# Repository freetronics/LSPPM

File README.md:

Freetronics LibreSat Payload Processor Module
=============================================
Copyright 2013-2017 Freetronics Pty Ltd  
Freetronics site:  www.freetronics.com  
Freetronics email: info@freetronics.com  

A CubeSat payload board that incorporates 16 processor nodes for
running experiments, and a supervisor processor node to control
the experiment nodes.

A previous version of this board flew in space on ArduSat-X and
ArduSat-1.

Features:

 * 16 x processor nodes, each with an ATmega328P MCU
 * Each processor node runs the Arduino bootloader
 * 1 x supervisor node with an ATmega2561
 * Micro SD card slot connected to supervisor
 * All MCUs and sensors on a shared I2C bus
 * All I2C devices use bidirectional isolation circuits to allow continued operation of the system with failed devices
 * Processor node UARTs connected via multiplexers to the supervisor's first UART
 * 5V serial debug console with standard FTDI-style pinout on supervisor's second UART
 * Each processor node can be powered down independently by the supervisor
 * Each processor node can be reset using an I2C latch by the supervisor
 * Each MCU has an independent crystal for maximum reliability
 * TX, RX, and D13 LEDs on every processor node
 * Top and bottom temperature sensors on I2C bus with "disable" option to prevent address collisions
 * Requires external 5V and 3.3V supply
 * Current consumption monitoring of both power rails by the supervisor
 * Stackable CubeSat bus connectors
 * Conforms to CubeSat mechanical standards for dimensions and mounting
 * Selectable power bus connections
 * Optional I2C satellite bus pull-ups
 * I2C headers for spectrometer, Geiger counter, and bottom plate sensor assembly
 * GPS header with UART connections to node 11 via 3.3V level shifters
 * Switchable power supply to GPS header controlled by supervisor
 * Stackable CubeSat Bus connectors

Specifications:

 * Dimensions: 95.45mm x 90.3mm
 * PCB material: FR4 fibreglass (requires out-gassing before vacuum use)
 * PCB finish: ENIG (electroless nickel immersion gold) recommended
 * Module mass: 37 grams
 * Connector mass (pair): 15 grams
 * Total assembled mass including solder: 54 grams

More information is available at:

  http://www.freetronics.com.au/lsppm

INSTALLATION
------------
The design is saved as an EAGLE project. EAGLE PCB design software is
available from www.cadsoftusa.com free for non-commercial use. To use
this project download it and place the directory containing these files
into the "eagle" directory on your computer. Then open EAGLE and
navigate to the project. 

DISTRIBUTION
------------
The specific terms of distribution of this project are governed by the
license referenced below.

LICENSE
-------
Licensed under the TAPR Open Hardware License (www.tapr.org/OHL).
The "license" folder within this repository also contains a copy of
this license in plain text format.

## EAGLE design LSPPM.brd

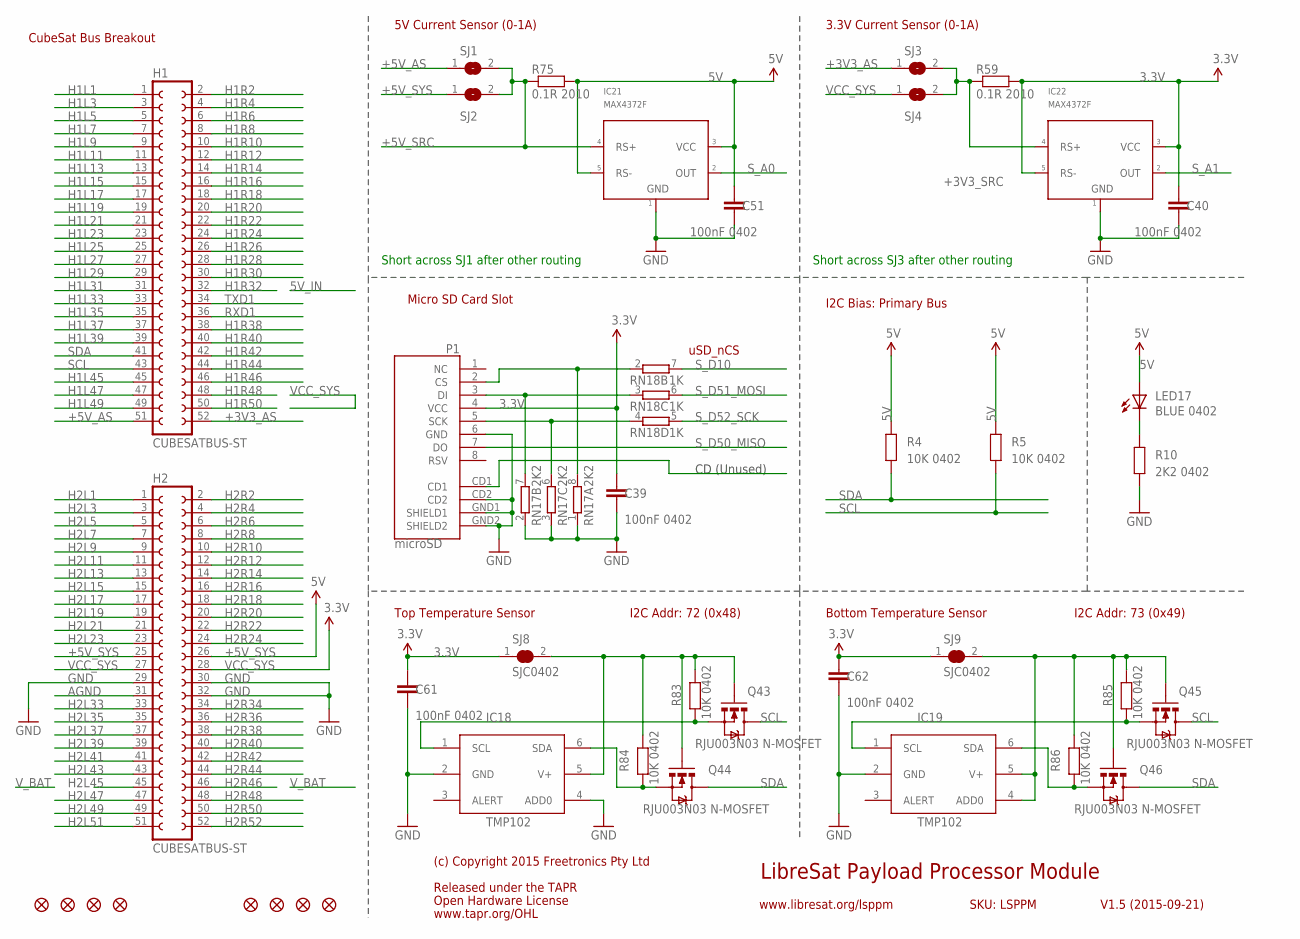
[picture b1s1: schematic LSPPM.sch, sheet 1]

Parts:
C39, C40, C51, C61, C62: 100nF 0402; C0402
FID1, FID2, FID3, FID4, FID5, FID6, FID7, FID8: FIDUCIAL1X2.5; FIDUCIAL-1X2.5
H1, H2: CUBESATBUS-ST
IC18, IC19: TMP102; SOT563
IC21, IC22: MAX4372F; SOT23-5
LED17: BLUE 0402; LED-0402
P1: microSD; MICRO-SD-SOCKET-PP
Q43, Q44, Q45, Q46: RJU003N03 N-MOSFET; SOT32-3
R4, R5, R83, R84, R85, R86: 10K 0402; R0402
R10: 2K2 0402; R0402
R59, R75: 0.1R 2010; R2010
RN17: 2K2; CAY16
RN18: 1K; CAY16
SJ1, SJ2, SJ3, SJ4: SJ
SJ8, SJ9: SJC0402; 0402SJC

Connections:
3.3V: C39.1, C40.1, C61.1, C62.1, IC22.3 (VCC), IC22.5 (RS-), P1.4 (VCC), R59.2, SJ8.1, SJ9.1; also elsewhere on the board
5V: C51.1, IC21.3 (VCC), IC21.5 (RS-), LED17.A, R4.2, R5.2, R75.2; also elsewhere on the board
+3V3_AS: H1.52, SJ3.1
+3V3_SRC: IC22.4 (RS+), R59.1, SJ3.2, SJ4.2
+5V_AS: H1.51, SJ1.1
+5V_SRC: IC21.4 (RS+), R75.1, SJ1.2, SJ2.2; also elsewhere on the board
+5V_SYS: H2.25, H2.26, SJ2.1
AGND: H2.31
GND: C39.2, C40.2, C51.2, C61.2, C62.2, H2.29, H2.30, H2.32, IC18.2 (GND), IC18.4 (ADD0), IC19.2 (GND), IC21.1 (GND), IC22.1 (GND), P1.6 (GND), P1.CD2, P1.GND1 (SHIELD1), P1.GND2 (SHIELD2), R10.1, RN17.1, RN17.2 (1), RN17.3 (1); also elsewhere on the board
H1L1: H1.1
H1L3: H1.3
H1L5: H1.5
H1L7: H1.7
H1L9: H1.9
H1L11: H1.11
H1L13: H1.13
H1L15: H1.15
H1L17: H1.17
H1L19: H1.19
H1L21: H1.21
H1L23: H1.23
H1L25: H1.25
H1L27: H1.27
H1L29: H1.29
H1L31: H1.31
H1L33: H1.33
H1L35: H1.35
H1L37: H1.37
H1L39: H1.39
H1L45: H1.45
H1L47: H1.47
H1L49: H1.49
H1R2: H1.2
H1R4: H1.4
H1R6: H1.6
H1R8: H1.8
H1R10: H1.10
H1R12: H1.12
H1R14: H1.14
H1R16: H1.16
H1R18: H1.18
H1R20: H1.20
H1R22: H1.22
H1R24: H1.24
H1R26: H1.26
H1R28: H1.28
H1R30: H1.30
H1R32: H1.32
H1R38: H1.38
H1R40: H1.40
H1R42: H1.42
H1R44: H1.44
H1R46: H1.46
H1R48: H1.48
H1R50: H1.50
H2L1: H2.1
H2L3: H2.3
H2L5: H2.5
H2L7: H2.7
H2L9: H2.9
H2L11: H2.11
H2L13: H2.13
H2L15: H2.15
H2L17: H2.17
H2L19: H2.19
H2L21: H2.21
H2L23: H2.23
H2L33: H2.33
H2L35: H2.35
H2L37: H2.37
H2L39: H2.39
H2L41: H2.41
H2L43: H2.43
H2L45: H2.45
H2L47: H2.47
H2L49: H2.49
H2L51: H2.51
H2R2: H2.2
H2R4: H2.4
H2R6: H2.6
H2R8: H2.8
H2R10: H2.10
H2R12: H2.12
H2R14: H2.14
H2R16: H2.16
H2R18: H2.18
H2R20: H2.20
H2R22: H2.22
H2R24: H2.24
H2R34: H2.34
H2R36: H2.36
H2R38: H2.38
H2R40: H2.40
H2R42: H2.42
H2R44: H2.44
H2R46: H2.46
H2R48: H2.48
H2R50: H2.50
H2R52: H2.52
unnamed: LED17.C, R10.2
unnamed: P1.2 (CS), RN17.8 (2), RN18.2 (1)
unnamed: P1.3 (DI), RN17.7 (2), RN18.3 (1)
unnamed: P1.5 (SCK), RN17.6 (2), RN18.4 (1)
unnamed: IC18.1 (SCL), Q43.2 (S), R83.1
unnamed: IC18.6 (SDA), Q44.2 (S), R84.1
unnamed: IC19.6 (SDA), Q46.2 (S), R86.1
unnamed: IC19.1 (SCL), Q45.2 (S), R85.1
unnamed: IC18.5 (V+), Q43.1 (G), Q44.1 (G), R83.2, R84.2, SJ8.2
unnamed: IC19.4 (ADD0), IC19.5 (V+), Q45.1 (G), Q46.1 (G), R85.2, R86.2, SJ9.2
RXD1: H1.36; also elsewhere on the board
SCL: H1.43, Q43.3 (D), Q45.3 (D), R5.1; also elsewhere on the board
SDA: H1.41, Q44.3 (D), Q46.3 (D), R4.1; also elsewhere on the board
S_A0: IC21.2 (OUT); also elsewhere on the board
S_A1: IC22.2 (OUT); also elsewhere on the board
S_D10: RN18.7 (2); also elsewhere on the board
S_D50_MISO: P1.7 (DO); also elsewhere on the board
S_D51_MOSI: RN18.6 (2); also elsewhere on the board
S_D52_SCK: RN18.5 (2); also elsewhere on the board
TXD1: H1.34; also elsewhere on the board
VCC_SYS: H2.27, H2.28, SJ4.1

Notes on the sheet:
LibreSat Payload Processor Module
V1.5 (2015-09-21)
www.libresat.org/lsppm
SKU: LSPPM
CubeSat Bus Breakout
Released under the TAPR
Open Hardware License
www.tapr.org/OHL
(c) Copyright 2015 Freetronics Pty Ltd
I2C Bias: Primary Bus
5V Current Sensor (0-1A)
3.3V Current Sensor (0-1A)
Top Temperature Sensor
Bottom Temperature Sensor
I2C Addr: 72 (0x48)
I2C Addr: 73 (0x49)
Short across SJ1 after other routing
uSD_nCS
Micro SD Card Slot
CD (Unused)
Short across SJ3 after other routing

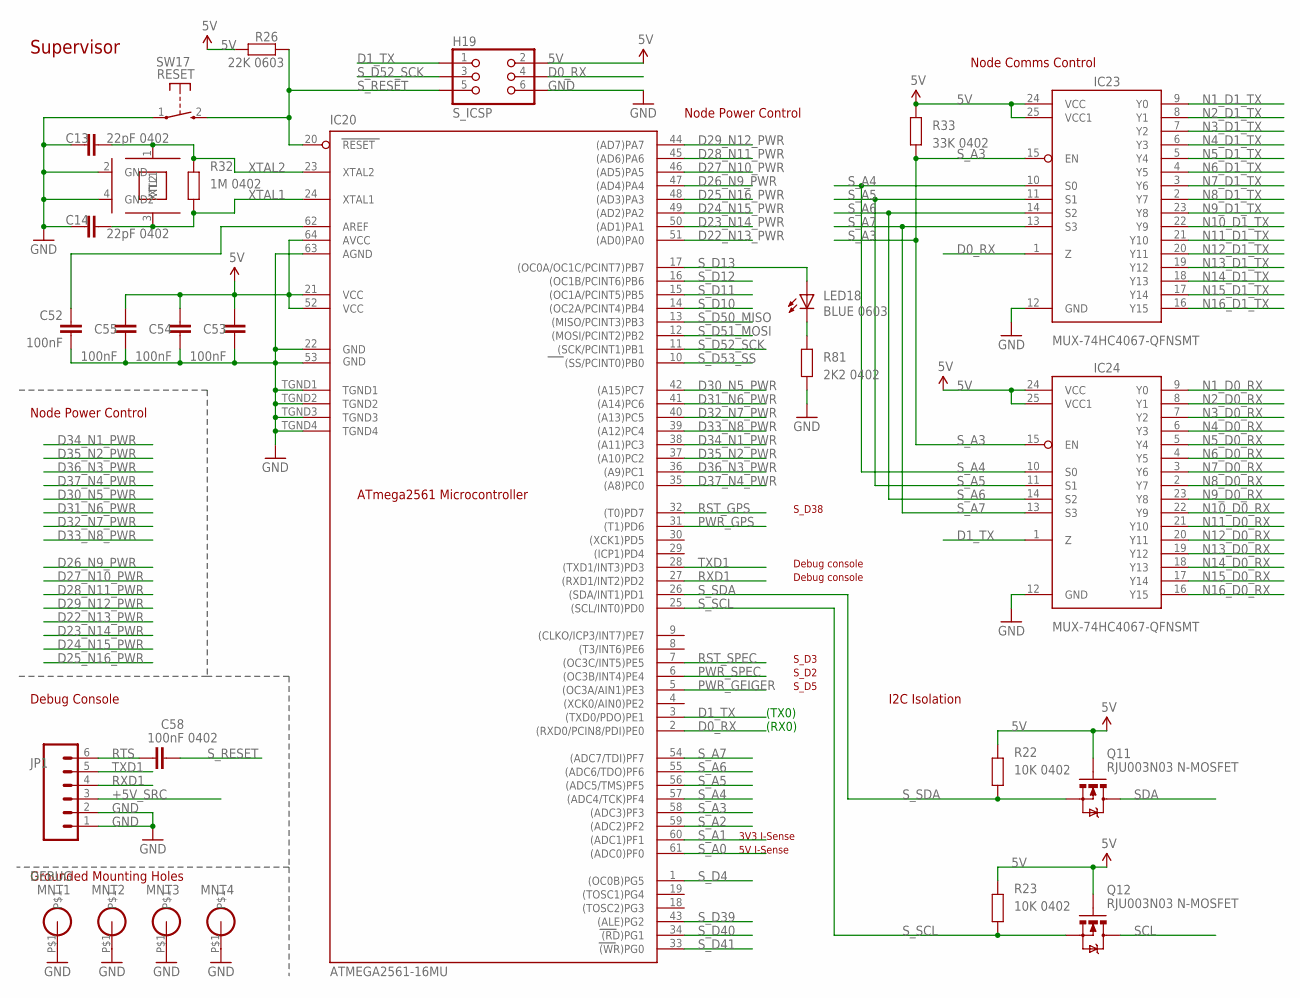
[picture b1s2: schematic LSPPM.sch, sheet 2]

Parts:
C13, C14: 22pF 0402; C0402
C52, C53, C54, C55: 100nF; C0402
C58: 100nF 0402; C0402
H19: S_ICSP; 2X03-ICSP
IC20: ATMEGA2561-16MU; MLF64
IC23, IC24: MUX-74HC4067-QFNSMT; DHVQFN24
JP1: DEBUG; 1X06-P-RA
LED18: BLUE 0603; LED-0402
MNT1, MNT2, MNT3, MNT4: HOLE3.2MM; HOLE32
Q11, Q12: RJU003N03 N-MOSFET; SOT32-3
R22, R23: 10K 0402; R0402
R26: 22K 0603; R0402
R32: 1M 0402; R0402
R33: 33K 0402; R0402
R81: 2K2 0402; R0402
SW17: RESET; TACTILE_SMT_3X4X2
XTL17: SMD3225-16MHZ 3.2 x 2.5mm crystal; CRYSTAL-SMD-3X2

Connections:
5V: C53.1, C54.1, C55.1, H19.2, IC20.21 (VCC), IC20.52 (VCC1), IC20.64 (AVCC), IC23.24 (VCC), IC23.25 (VCC1), IC24.24 (VCC), IC24.25 (VCC1), Q11.1 (G), Q12.1 (G), R22.2, R23.2, R26.2, R33.2; also elsewhere on the board
+5V_SRC: JP1.3; also elsewhere on the board
D0_RX: H19.4, IC20.2 ((RXD0/PCIN8/PDI)PE0), IC23.1 (Z)
D1_TX: H19.1, IC20.3 ((TXD0/PDO)PE1), IC24.1 (Z)
D22_N13_PWR: IC20.51 ((AD0)PA0); also elsewhere on the board
D23_N14_PWR: IC20.50 ((AD1)PA1); also elsewhere on the board
D24_N15_PWR: IC20.49 ((AD2)PA2); also elsewhere on the board
D25_N16_PWR: IC20.48 ((AD3)PA3); also elsewhere on the board
D26_N9_PWR: IC20.47 ((AD4)PA4); also elsewhere on the board
D27_N10_PWR: IC20.46 ((AD5)PA5); also elsewhere on the board
D28_N11_PWR: IC20.45 ((AD6)PA6); also elsewhere on the board
D29_N12_PWR: IC20.44 ((AD7)PA7); also elsewhere on the board
D30_N5_PWR: IC20.42 ((A15)PC7); also elsewhere on the board
D31_N6_PWR: IC20.41 ((A14)PC6); also elsewhere on the board
D32_N7_PWR: IC20.40 ((A13)PC5); also elsewhere on the board
D33_N8_PWR: IC20.39 ((A12)PC4); also elsewhere on the board
D34_N1_PWR: IC20.38 ((A11)PC3); also elsewhere on the board
D35_N2_PWR: IC20.37 ((A10)PC2); also elsewhere on the board
D36_N3_PWR: IC20.36 ((A9)PC1); also elsewhere on the board
D37_N4_PWR: IC20.35 ((A8)PC0); also elsewhere on the board
GND: C13.1, C14.1, C52.2, C53.2, C54.2, C55.2, H19.6, IC20.22 (GND), IC20.53 (GND1), IC20.63 (AGND), IC20.TGND1, IC20.TGND2, IC20.TGND3, IC20.TGND4, IC23.12 (GND), IC24.12 (GND), JP1.1, JP1.2, MNT1.P$1, MNT2.P$1, MNT3.P$1, MNT4.P$1, R81.1, SW17.1, XTL17.2 (GND), XTL17.4 (GND2); also elsewhere on the board
N1_D0_RX: IC24.9 (Y0); also elsewhere on the board
N1_D1_TX: IC23.9 (Y0); also elsewhere on the board
N2_D0_RX: IC24.8 (Y1); also elsewhere on the board
N2_D1_TX: IC23.8 (Y1); also elsewhere on the board
N3_D0_RX: IC24.7 (Y2); also elsewhere on the board
N3_D1_TX: IC23.7 (Y2); also elsewhere on the board
N4_D0_RX: IC24.6 (Y3); also elsewhere on the board
N4_D1_TX: IC23.6 (Y3); also elsewhere on the board
N5_D0_RX: IC24.5 (Y4); also elsewhere on the board
N5_D1_TX: IC23.5 (Y4); also elsewhere on the board
N6_D0_RX: IC24.4 (Y5); also elsewhere on the board
N6_D1_TX: IC23.4 (Y5); also elsewhere on the board
N7_D0_RX: IC24.3 (Y6); also elsewhere on the board
N7_D1_TX: IC23.3 (Y6); also elsewhere on the board
N8_D0_RX: IC24.2 (Y7); also elsewhere on the board
N8_D1_TX: IC23.2 (Y7); also elsewhere on the board
N9_D0_RX: IC24.23 (Y8); also elsewhere on the board
N9_D1_TX: IC23.23 (Y8); also elsewhere on the board
N10_D0_RX: IC24.22 (Y9); also elsewhere on the board
N10_D1_TX: IC23.22 (Y9); also elsewhere on the board
N11_D0_RX: IC24.21 (Y10); also elsewhere on the board
N11_D1_TX: IC23.21 (Y10); also elsewhere on the board
N12_D0_RX: IC24.20 (Y11); also elsewhere on the board
N12_D1_TX: IC23.20 (Y11); also elsewhere on the board
N13_D0_RX: IC24.19 (Y12); also elsewhere on the board
N13_D1_TX: IC23.19 (Y12); also elsewhere on the board
N14_D0_RX: IC24.18 (Y13); also elsewhere on the board
N14_D1_TX: IC23.18 (Y13); also elsewhere on the board
N15_D0_RX: IC24.17 (Y14); also elsewhere on the board
N15_D1_TX: IC23.17 (Y14); also elsewhere on the board
N16_D0_RX: IC24.16 (Y15); also elsewhere on the board
N16_D1_TX: IC23.16 (Y15); also elsewhere on the board
unnamed: C52.1, IC20.62 (AREF)
unnamed: LED18.C, R81.2
PWR_GEIGER: IC20.5 ((OC3A/AIN1)PE3); also elsewhere on the board
PWR_GPS: IC20.31 ((T1)PD6); also elsewhere on the board
PWR_SPEC: IC20.6 ((OC3B/INT4)PE4); also elsewhere on the board
RST_GPS: IC20.32 ((T0)PD7); also elsewhere on the board
RST_SPEC: IC20.7 ((OC3C/INT5)PE5); also elsewhere on the board
RTS: C58.1, JP1.6
RXD1: IC20.27 ((RXD1/INT2)PD2), JP1.4; also elsewhere on the board
SCL: Q12.3 (D); also elsewhere on the board
SDA: Q11.3 (D); also elsewhere on the board
S_A0: IC20.61 ((ADC0)PF0); also elsewhere on the board
S_A1: IC20.60 ((ADC1)PF1); also elsewhere on the board
S_A2: IC20.59 ((ADC2)PF2)
S_A3: IC20.58 ((ADC3)PF3), IC23.15 (EN), IC24.15 (EN), R33.1
S_A4: IC20.57 ((ADC4/TCK)PF4), IC23.10 (S0), IC24.10 (S0)
S_A5: IC20.56 ((ADC5/TMS)PF5), IC23.11 (S1), IC24.11 (S1)
S_A6: IC20.55 ((ADC6/TDO)PF6), IC23.14 (S2), IC24.14 (S2)
S_A7: IC20.54 ((ADC7/TDI)PF7), IC23.13 (S3), IC24.13 (S3)
S_D4: IC20.1 ((OC0B)PG5)
S_D10: IC20.14 ((OC2A/PCINT4)PB4); also elsewhere on the board
S_D11: IC20.15 ((OC1A/PCINT5)PB5)
S_D12: IC20.16 ((OC1B/PCINT6)PB6)
S_D13: IC20.17 ((OC0A/OC1C/PCINT7)PB7), LED18.A
S_D39: IC20.43 ((ALE)PG2)
S_D40: IC20.34 ((RD)PG1)
S_D41: IC20.33 ((WR)PG0)
S_D50_MISO: IC20.13 ((MISO/PCINT3)PB3); also elsewhere on the board
S_D51_MOSI: IC20.12 ((MOSI/PCINT2)PB2); also elsewhere on the board
S_D52_SCK: H19.3, IC20.11 ((SCK/PCINT1)PB1); also elsewhere on the board
S_D53_SS: IC20.10 ((SS/PCINT0)PB0)
S_RESET: C58.2, H19.5, IC20.20 (RESET), R26.1, SW17.2 (S)
S_SCL: IC20.25 ((SCL/INT0)PD0), Q12.2 (S), R23.1
S_SDA: IC20.26 ((SDA/INT1)PD1), Q11.2 (S), R22.1
TXD1: IC20.28 ((TXD1/INT3)PD3), JP1.5; also elsewhere on the board
XTAL1: C14.2, IC20.24 (XTAL1), R32.1, XTL17.3 (XTL2)
XTAL2: C13.2, IC20.23 (XTAL2), R32.2, XTL17.1 (XTL1)

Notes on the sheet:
Supervisor
Node Comms Control
Node Power Control
I2C Isolation
ATmega2561 Microcontroller
(TX0)
(RX0)
Grounded Mounting Holes
Debug Console
5V I-Sense
3V3 I-Sense
S_D5
S_D2
S_D3
Debug console
S_D38

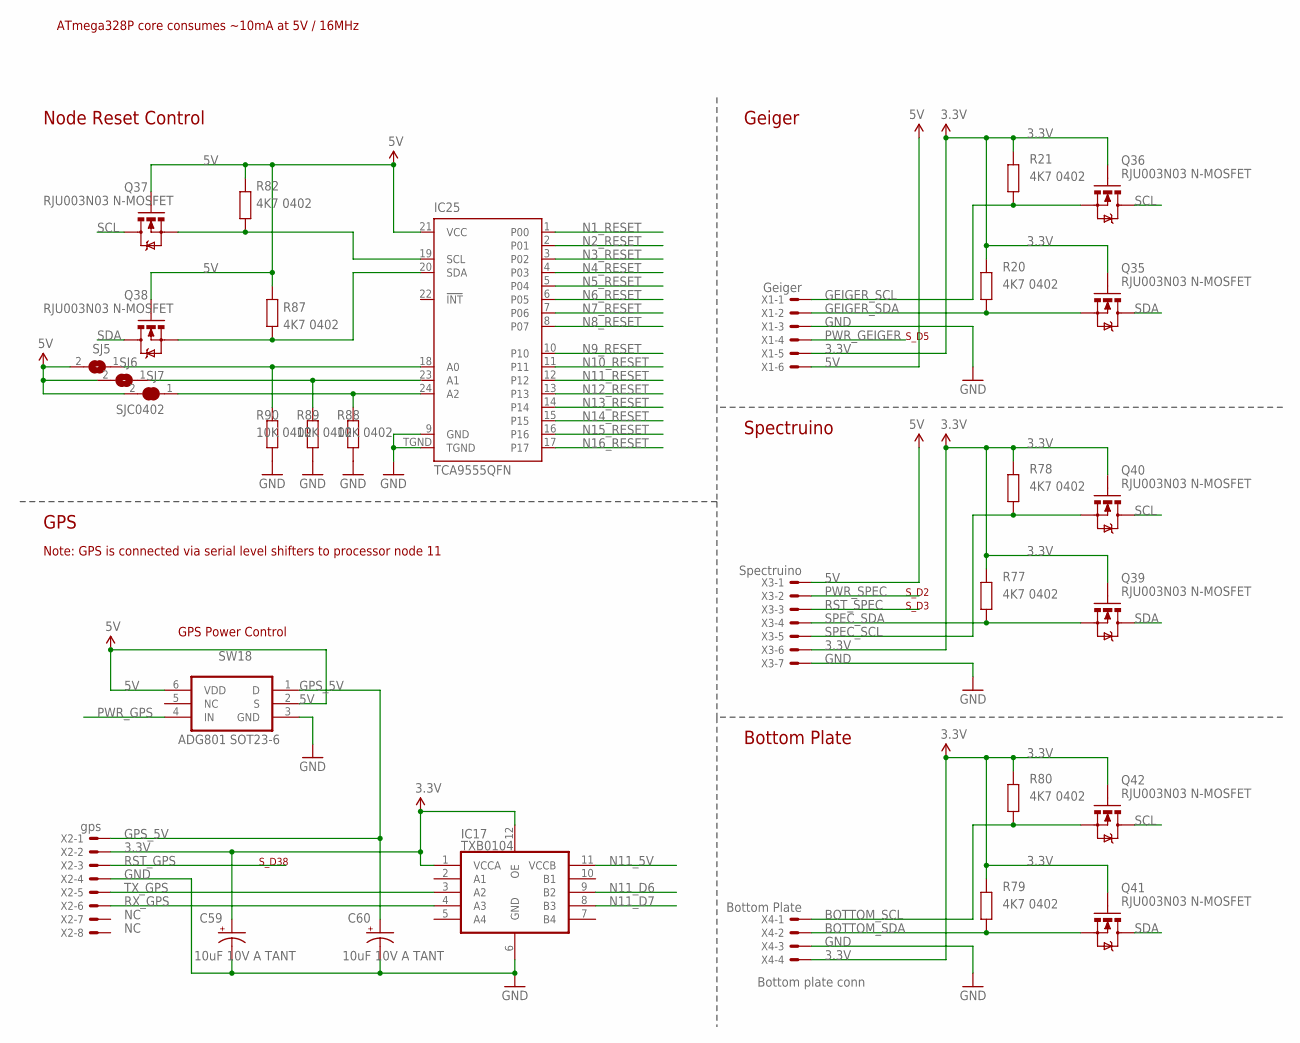
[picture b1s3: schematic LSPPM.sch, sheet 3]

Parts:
C59, C60: 10uF 10V A TANT; EIA3216
IC17: TXB0104; QFN-12
IC25: TCA9555QFN; QFN-24
Q35, Q36, Q37, Q38, Q39, Q40, Q41, Q42: RJU003N03 N-MOSFET; SOT32-3
R20, R21, R77, R78, R79, R80, R82, R87: 4K7 0402; R0402
R88, R89, R90: 10K 0402; R0402
SJ5, SJ6: SJ0402O; 0402SJO
SJ7: SJC0402; 0402SJC
SW18: ADG801 SOT23-6; SOT23-6
X1: Geiger; 53398-06
X2: gps; 53398-08
X3: Spectruino; 53398-07
X4: Bottom Plate; 53398-04

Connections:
3.3V: C59.A (+), IC17.1 (VCCA), IC17.12 (OE), Q35.1 (G), Q36.1 (G), Q39.1 (G), Q40.1 (G), Q41.1 (G), Q42.1 (G), R20.2, R21.2, R77.2, R78.2, R79.2, R80.2, X1.5, X2.2, X3.6, X4.4; also elsewhere on the board
5V: IC25.21 (VCC), Q37.1 (G), Q38.1 (G), R82.2, R87.2, SJ5.2, SJ6.2, SJ7.2, SW18.2 (S), SW18.6 (VDD), X1.6, X3.1; also elsewhere on the board
BOTTOM_SCL: Q42.2 (S), R80.1, X4.1
BOTTOM_SDA: Q41.2 (S), R79.1, X4.2
GEIGER_SCL: Q36.2 (S), R21.1, X1.1
GEIGER_SDA: Q35.2 (S), R20.1, X1.2
GND: C59.C (-), C60.C (-), IC17.6 (GND), IC25.9 (GND), IC25.TGND, R88.1, R89.1, R90.1, SW18.3 (GND), X1.3, X2.4, X3.7, X4.3; also elsewhere on the board
GPS_5V: C60.A (+), SW18.1 (D), X2.1
N1_RESET: IC25.1 (P00); also elsewhere on the board
N2_RESET: IC25.2 (P01); also elsewhere on the board
N3_RESET: IC25.3 (P02); also elsewhere on the board
N4_RESET: IC25.4 (P03); also elsewhere on the board
N5_RESET: IC25.5 (P04); also elsewhere on the board
N6_RESET: IC25.6 (P05); also elsewhere on the board
N7_RESET: IC25.7 (P06); also elsewhere on the board
N8_RESET: IC25.8 (P07); also elsewhere on the board
N9_RESET: IC25.10; also elsewhere on the board
N10_RESET: IC25.11; also elsewhere on the board
N11_5V: IC17.11 (VCCB); also elsewhere on the board
N11_D6: IC17.9 (B2); also elsewhere on the board
N11_D7: IC17.8 (B3); also elsewhere on the board
N11_RESET: IC25.12; also elsewhere on the board
N12_RESET: IC25.13; also elsewhere on the board
N13_RESET: IC25.14; also elsewhere on the board
N14_RESET: IC25.15; also elsewhere on the board
N15_RESET: IC25.16; also elsewhere on the board
N16_RESET: IC25.17; also elsewhere on the board
unnamed: IC25.18 (A0), R90.2, SJ5.1
unnamed: IC25.23 (A1), R89.2, SJ6.1
unnamed: IC25.24 (A2), R88.2, SJ7.1
unnamed: IC25.19 (SCL), Q37.2 (S), R82.1
unnamed: IC25.20 (SDA), Q38.2 (S), R87.1
PWR_GEIGER: X1.4; also elsewhere on the board
PWR_GPS: SW18.4 (IN); also elsewhere on the board
PWR_SPEC: X3.2; also elsewhere on the board
RST_GPS: X2.3; also elsewhere on the board
RST_SPEC: X3.3; also elsewhere on the board
RX_GPS: IC17.4 (A3), X2.6
SCL: Q36.3 (D), Q37.3 (D), Q40.3 (D), Q42.3 (D); also elsewhere on the board
SDA: Q35.3 (D), Q38.3 (D), Q39.3 (D), Q41.3 (D); also elsewhere on the board
SPEC_SCL: Q40.2 (S), R78.1, X3.5
SPEC_SDA: Q39.2 (S), R77.1, X3.4
TX_GPS: IC17.3 (A2), X2.5

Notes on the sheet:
Node Reset Control
Bottom plate conn
Geiger
Spectruino
Bottom Plate
GPS
Note: GPS is connected via serial level shifters to processor node 11
S_D3
S_D2
S_D5
ATmega328P core consumes ~10mA at 5V / 16MHz
S_D38
GPS Power Control

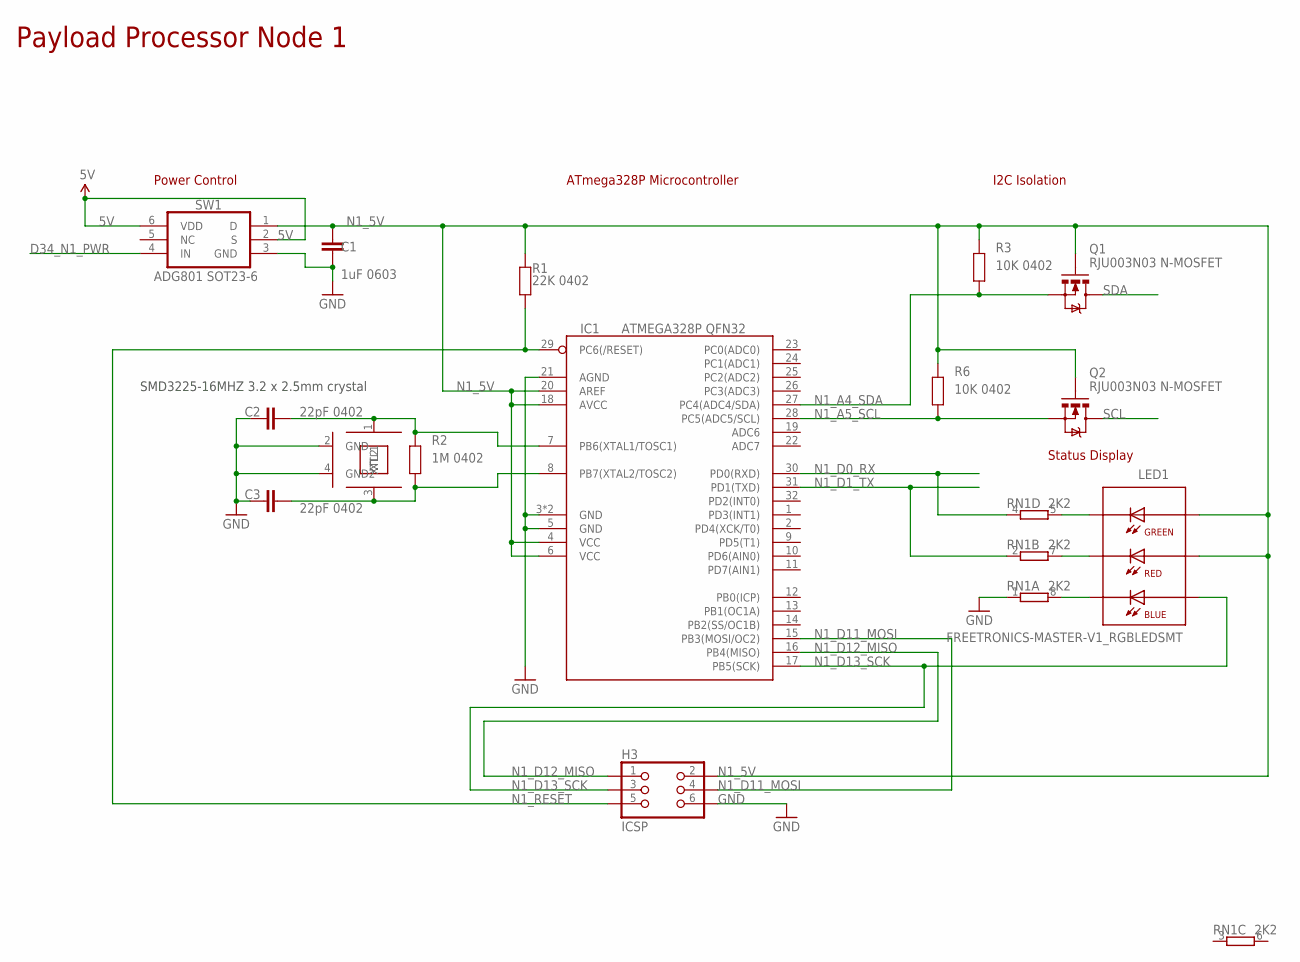
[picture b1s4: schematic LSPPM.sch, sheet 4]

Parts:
C1: 1uF 0603; C0603
C2, C3: 22pF 0402; C0402
H3: ICSP; M2X3-2MM
IC1: ATMEGA328P QFN32; MLF32
LED1: FREETRONICS-MASTER-V1_RGBLEDSMT; FREETRONICS-MASTER-V1_19-337
Q1, Q2: RJU003N03 N-MOSFET; SOT32-3
R1: 22K 0402; R0402
R2: 1M 0402; R0402
R3, R6: 10K 0402; R0402
RN1: 2K2; CAY16
SW1: ADG801 SOT23-6; SOT23-6
XTL1: SMD3225-16MHZ 3.2 x 2.5mm crystal; CRYSTAL-SMD-3X2

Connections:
5V: SW1.2 (S), SW1.6 (VDD); also elsewhere on the board
D34_N1_PWR: SW1.4 (IN); also elsewhere on the board
GND: C1.2, C2.1, C3.1, H3.6, IC1.3 (GND), IC1.5 (GND), IC1.21 (AGND), IC1.TGND (GND), RN1.1, SW1.3 (GND), XTL1.2 (GND), XTL1.4 (GND2); also elsewhere on the board
N1_5V: C1.1, H3.2, IC1.4 (VCC), IC1.6 (VCC), IC1.18 (AVCC), IC1.20 (AREF), LED1.5 (A-R), LED1.6 (A-G), Q1.1 (G), Q2.1 (G), R1.2, R3.2, R6.2, SW1.1 (D)
N1_A4_SDA: IC1.27 (PC4(ADC4/SDA)), Q1.2 (S), R3.1
N1_A5_SCL: IC1.28 (PC5(ADC5/SCL)), Q2.2 (S), R6.1
N1_D0_RX: IC1.30 (PD0(RXD)), RN1.4 (1); also elsewhere on the board
N1_D1_TX: IC1.31 (PD1(TXD)), RN1.2 (1); also elsewhere on the board
N1_D11_MOSI: H3.4, IC1.15 (PB3(MOSI/OC2))
N1_D12_MISO: H3.1, IC1.16 (PB4(MISO))
N1_D13_SCK: H3.3, IC1.17 (PB5(SCK)), LED1.4 (A-B)
N1_RESET: H3.5, IC1.29 (PC6(/RESET)), R1.1; also elsewhere on the board
unnamed: LED1.3 (C-G), RN1.5 (2)
unnamed: C3.2, IC1.8 (PB7(XTAL2/TOSC2)), R2.1, XTL1.3 (XTL2)
unnamed: C2.2, IC1.7 (PB6(XTAL1/TOSC1)), R2.2, XTL1.1 (XTL1)
unnamed: LED1.2 (C-R), RN1.7 (2)
unnamed: LED1.1 (C-B), RN1.8 (2)
SCL: Q2.3 (D); also elsewhere on the board
SDA: Q1.3 (D); also elsewhere on the board

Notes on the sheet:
Payload Processor Node 1
ATmega328P Microcontroller
I2C Isolation
Status Display
Power Control
SMD3225-16MHZ 3.2 x 2.5mm crystal

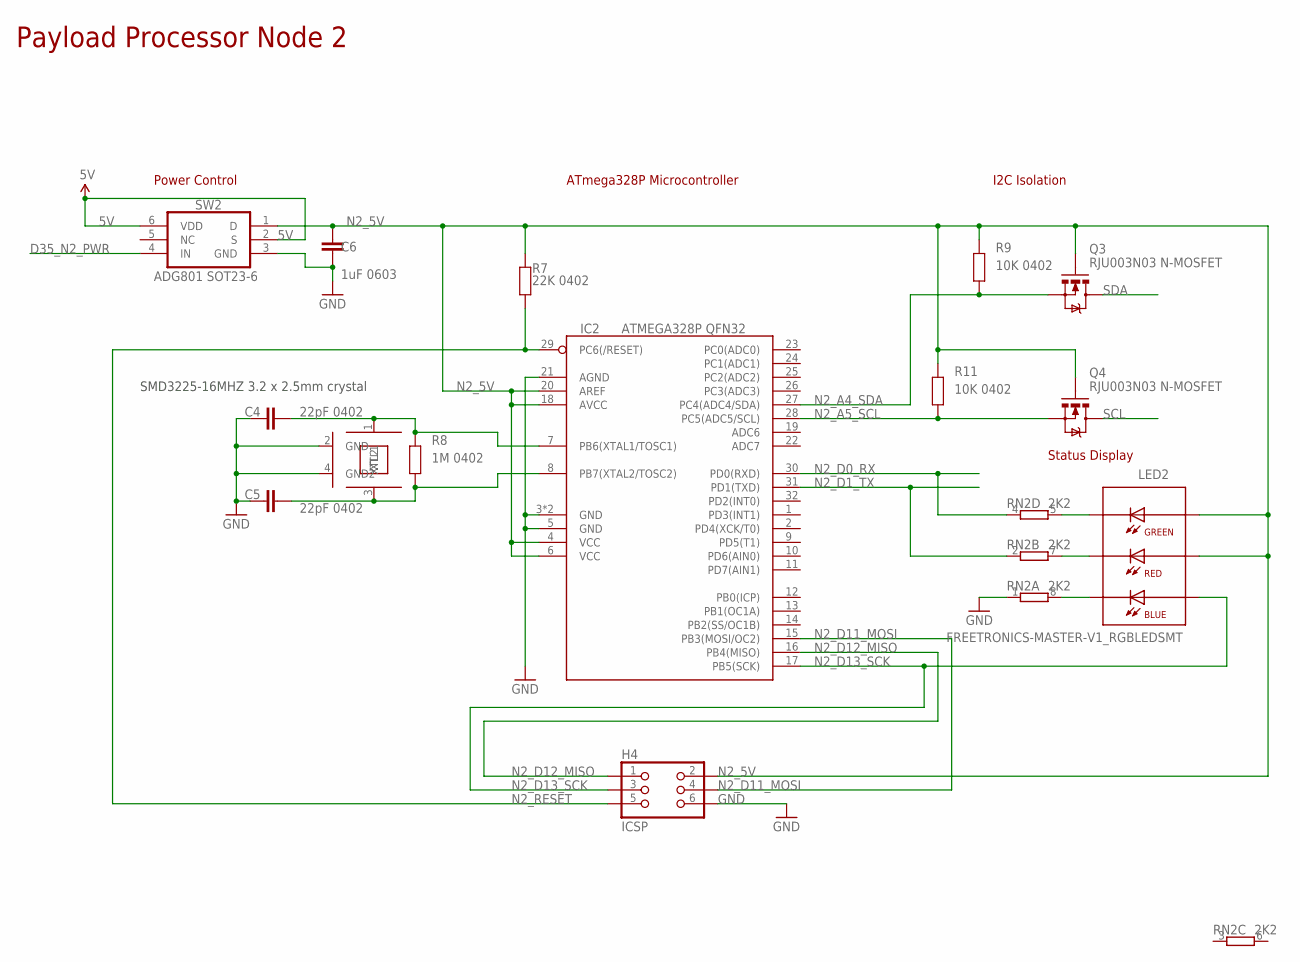
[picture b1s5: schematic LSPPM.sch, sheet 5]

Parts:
C4, C5: 22pF 0402; C0402
C6: 1uF 0603; C0603
H4: ICSP; M2X3-2MM
IC2: ATMEGA328P QFN32; MLF32
LED2: FREETRONICS-MASTER-V1_RGBLEDSMT; FREETRONICS-MASTER-V1_19-337
Q3, Q4: RJU003N03 N-MOSFET; SOT32-3
R7: 22K 0402; R0402
R8: 1M 0402; R0402
R9, R11: 10K 0402; R0402
RN2: 2K2; CAY16
SW2: ADG801 SOT23-6; SOT23-6
XTL2: SMD3225-16MHZ 3.2 x 2.5mm crystal; CRYSTAL-SMD-3X2

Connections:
5V: SW2.2 (S), SW2.6 (VDD); also elsewhere on the board
D35_N2_PWR: SW2.4 (IN); also elsewhere on the board
GND: C4.1, C5.1, C6.2, H4.6, IC2.3 (GND), IC2.5 (GND), IC2.21 (AGND), IC2.TGND (GND), RN2.1, SW2.3 (GND), XTL2.2 (GND), XTL2.4 (GND2); also elsewhere on the board
N2_5V: C6.1, H4.2, IC2.4 (VCC), IC2.6 (VCC), IC2.18 (AVCC), IC2.20 (AREF), LED2.5 (A-R), LED2.6 (A-G), Q3.1 (G), Q4.1 (G), R7.2, R9.2, R11.2, SW2.1 (D)
N2_A4_SDA: IC2.27 (PC4(ADC4/SDA)), Q3.2 (S), R9.1
N2_A5_SCL: IC2.28 (PC5(ADC5/SCL)), Q4.2 (S), R11.1
N2_D0_RX: IC2.30 (PD0(RXD)), RN2.4 (1); also elsewhere on the board
N2_D1_TX: IC2.31 (PD1(TXD)), RN2.2 (1); also elsewhere on the board
N2_D11_MOSI: H4.4, IC2.15 (PB3(MOSI/OC2))
N2_D12_MISO: H4.1, IC2.16 (PB4(MISO))
N2_D13_SCK: H4.3, IC2.17 (PB5(SCK)), LED2.4 (A-B)
N2_RESET: H4.5, IC2.29 (PC6(/RESET)), R7.1; also elsewhere on the board
unnamed: C5.2, IC2.8 (PB7(XTAL2/TOSC2)), R8.1, XTL2.3 (XTL2)
unnamed: C4.2, IC2.7 (PB6(XTAL1/TOSC1)), R8.2, XTL2.1 (XTL1)
unnamed: LED2.2 (C-R), RN2.7 (2)
unnamed: LED2.1 (C-B), RN2.8 (2)
unnamed: LED2.3 (C-G), RN2.5 (2)
SCL: Q4.3 (D); also elsewhere on the board
SDA: Q3.3 (D); also elsewhere on the board

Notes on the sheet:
Payload Processor Node 2
ATmega328P Microcontroller
I2C Isolation
Status Display
Power Control
SMD3225-16MHZ 3.2 x 2.5mm crystal

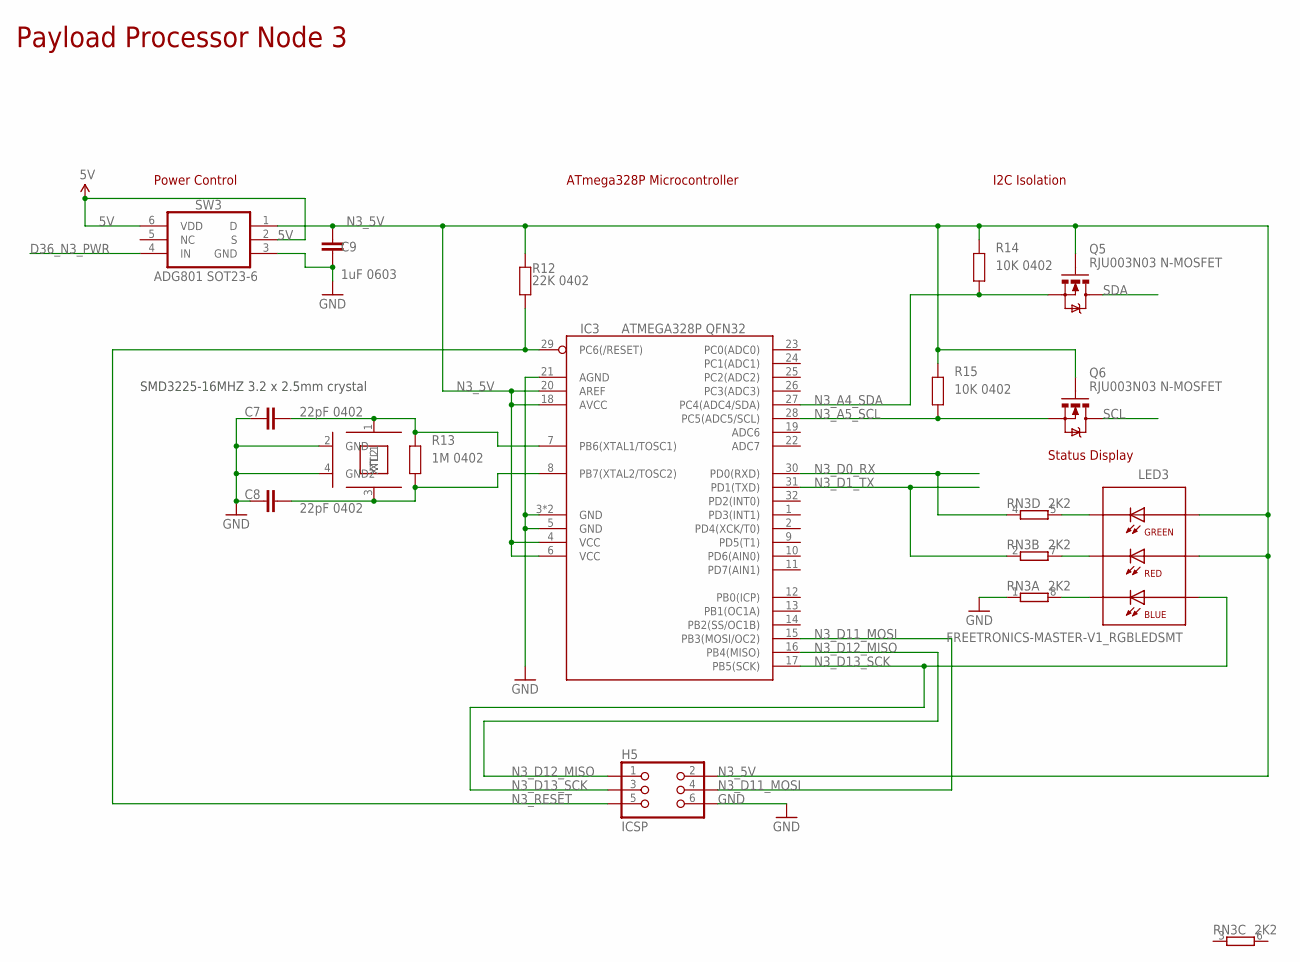
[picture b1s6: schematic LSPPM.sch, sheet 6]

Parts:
C7, C8: 22pF 0402; C0402
C9: 1uF 0603; C0603
H5: ICSP; M2X3-2MM
IC3: ATMEGA328P QFN32; MLF32
LED3: FREETRONICS-MASTER-V1_RGBLEDSMT; FREETRONICS-MASTER-V1_19-337
Q5, Q6: RJU003N03 N-MOSFET; SOT32-3
R12: 22K 0402; R0402
R13: 1M 0402; R0402
R14, R15: 10K 0402; R0402
RN3: 2K2; CAY16
SW3: ADG801 SOT23-6; SOT23-6
XTL3: SMD3225-16MHZ 3.2 x 2.5mm crystal; CRYSTAL-SMD-3X2

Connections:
5V: SW3.2 (S), SW3.6 (VDD); also elsewhere on the board
D36_N3_PWR: SW3.4 (IN); also elsewhere on the board
GND: C7.1, C8.1, C9.2, H5.6, IC3.3 (GND), IC3.5 (GND), IC3.21 (AGND), IC3.TGND (GND), RN3.1, SW3.3 (GND), XTL3.2 (GND), XTL3.4 (GND2); also elsewhere on the board
N3_5V: C9.1, H5.2, IC3.4 (VCC), IC3.6 (VCC), IC3.18 (AVCC), IC3.20 (AREF), LED3.5 (A-R), LED3.6 (A-G), Q5.1 (G), Q6.1 (G), R12.2, R14.2, R15.2, SW3.1 (D)
N3_A4_SDA: IC3.27 (PC4(ADC4/SDA)), Q5.2 (S), R14.1
N3_A5_SCL: IC3.28 (PC5(ADC5/SCL)), Q6.2 (S), R15.1
N3_D0_RX: IC3.30 (PD0(RXD)), RN3.4 (1); also elsewhere on the board
N3_D1_TX: IC3.31 (PD1(TXD)), RN3.2 (1); also elsewhere on the board
N3_D11_MOSI: H5.4, IC3.15 (PB3(MOSI/OC2))
N3_D12_MISO: H5.1, IC3.16 (PB4(MISO))
N3_D13_SCK: H5.3, IC3.17 (PB5(SCK)), LED3.4 (A-B)
N3_RESET: H5.5, IC3.29 (PC6(/RESET)), R12.1; also elsewhere on the board
unnamed: C8.2, IC3.8 (PB7(XTAL2/TOSC2)), R13.1, XTL3.3 (XTL2)
unnamed: C7.2, IC3.7 (PB6(XTAL1/TOSC1)), R13.2, XTL3.1 (XTL1)
unnamed: LED3.2 (C-R), RN3.7 (2)
unnamed: LED3.1 (C-B), RN3.8 (2)
unnamed: LED3.3 (C-G), RN3.5 (2)
SCL: Q6.3 (D); also elsewhere on the board
SDA: Q5.3 (D); also elsewhere on the board

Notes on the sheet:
Payload Processor Node 3
ATmega328P Microcontroller
I2C Isolation
Status Display
Power Control
SMD3225-16MHZ 3.2 x 2.5mm crystal

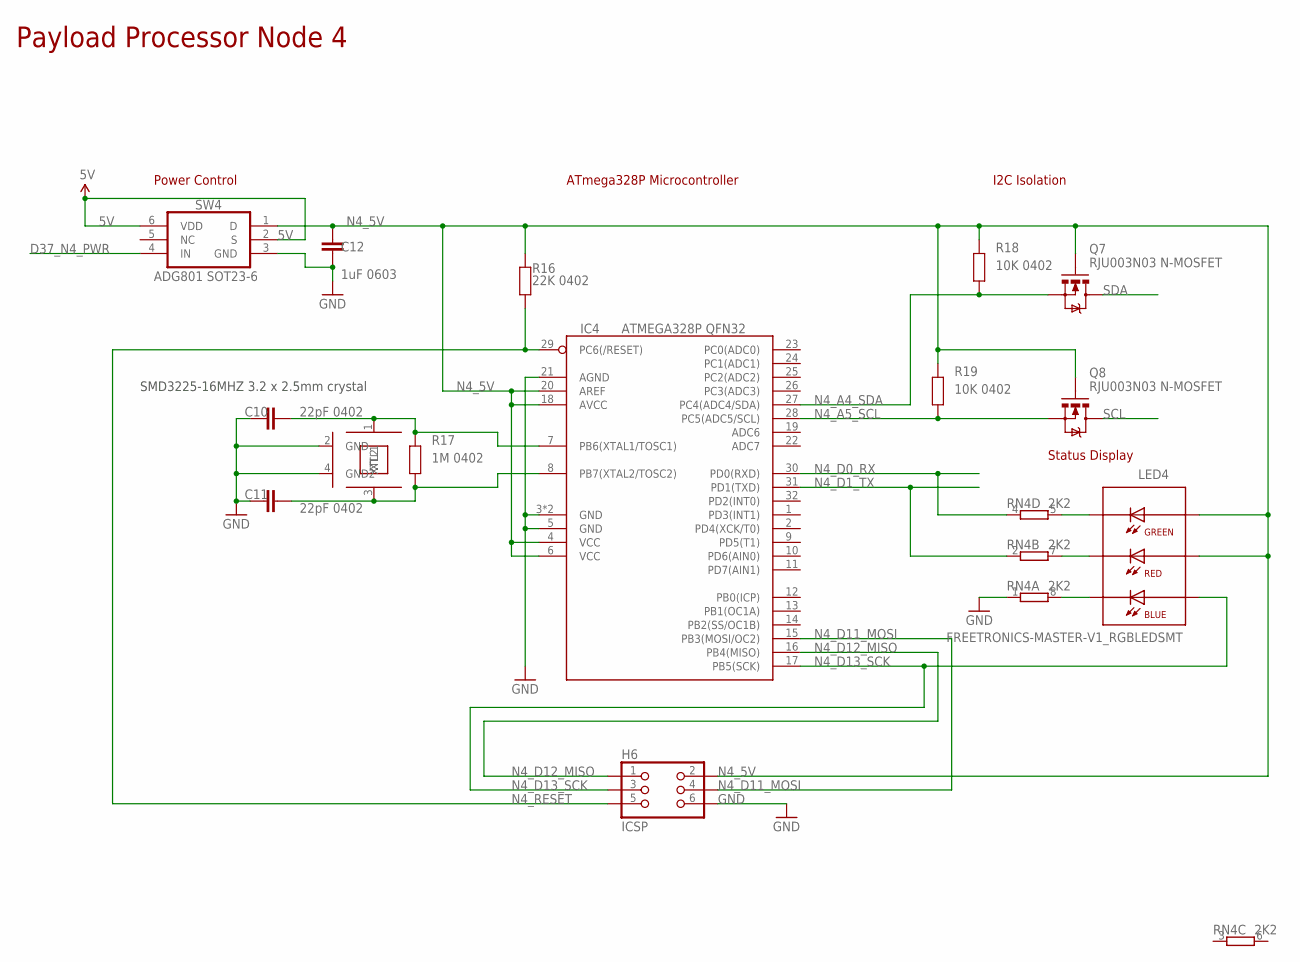
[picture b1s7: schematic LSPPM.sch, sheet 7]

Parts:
C10, C11: 22pF 0402; C0402
C12: 1uF 0603; C0603
H6: ICSP; M2X3-2MM
IC4: ATMEGA328P QFN32; MLF32
LED4: FREETRONICS-MASTER-V1_RGBLEDSMT; FREETRONICS-MASTER-V1_19-337
Q7, Q8: RJU003N03 N-MOSFET; SOT32-3
R16: 22K 0402; R0402
R17: 1M 0402; R0402
R18, R19: 10K 0402; R0402
RN4: 2K2; CAY16
SW4: ADG801 SOT23-6; SOT23-6
XTL4: SMD3225-16MHZ 3.2 x 2.5mm crystal; CRYSTAL-SMD-3X2

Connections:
5V: SW4.2 (S), SW4.6 (VDD); also elsewhere on the board
D37_N4_PWR: SW4.4 (IN); also elsewhere on the board
GND: C10.1, C11.1, C12.2, H6.6, IC4.3 (GND), IC4.5 (GND), IC4.21 (AGND), IC4.TGND (GND), RN4.1, SW4.3 (GND), XTL4.2 (GND), XTL4.4 (GND2); also elsewhere on the board
N4_5V: C12.1, H6.2, IC4.4 (VCC), IC4.6 (VCC), IC4.18 (AVCC), IC4.20 (AREF), LED4.5 (A-R), LED4.6 (A-G), Q7.1 (G), Q8.1 (G), R16.2, R18.2, R19.2, SW4.1 (D)
N4_A4_SDA: IC4.27 (PC4(ADC4/SDA)), Q7.2 (S), R18.1
N4_A5_SCL: IC4.28 (PC5(ADC5/SCL)), Q8.2 (S), R19.1
N4_D0_RX: IC4.30 (PD0(RXD)), RN4.4 (1); also elsewhere on the board
N4_D1_TX: IC4.31 (PD1(TXD)), RN4.2 (1); also elsewhere on the board
N4_D11_MOSI: H6.4, IC4.15 (PB3(MOSI/OC2))
N4_D12_MISO: H6.1, IC4.16 (PB4(MISO))
N4_D13_SCK: H6.3, IC4.17 (PB5(SCK)), LED4.4 (A-B)
N4_RESET: H6.5, IC4.29 (PC6(/RESET)), R16.1; also elsewhere on the board
unnamed: C11.2, IC4.8 (PB7(XTAL2/TOSC2)), R17.1, XTL4.3 (XTL2)
unnamed: C10.2, IC4.7 (PB6(XTAL1/TOSC1)), R17.2, XTL4.1 (XTL1)
unnamed: LED4.2 (C-R), RN4.7 (2)
unnamed: LED4.1 (C-B), RN4.8 (2)
unnamed: LED4.3 (C-G), RN4.5 (2)
SCL: Q8.3 (D); also elsewhere on the board
SDA: Q7.3 (D); also elsewhere on the board

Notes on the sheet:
Payload Processor Node 4
ATmega328P Microcontroller
I2C Isolation
Status Display
Power Control
SMD3225-16MHZ 3.2 x 2.5mm crystal

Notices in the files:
ArduSatMultipleProcessorModule.brd:
(c) 2012 Freetronics Pty Ltd
LSPPM.brd:
Copyright 2013 Freetronics Pty Ltd
Open Hardware Licence
parts and their libraries:
freetronics-original: Licensing: CC v3.0 Share-Alike You are welcome to use this library for commercial purposes.
